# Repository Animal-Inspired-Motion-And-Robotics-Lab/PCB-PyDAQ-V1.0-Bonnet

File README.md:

# Raspberry Pi Data Conversion Board (ADC, DAC, PWM)

<br/>
<br/>

## Description

This board turns your Raspberry Pi into a prototyping powerhouse!  Now your Raspberry Pi can both read and generate analog voltages, in addition to driving PWM waveforms all using existing Python libraries! This repository includes all design files needed to immediately order and assemble the board or make further modifications!

## Features

- 26 Pin IDC Connector for easy prototyping
- 2x STEMMA QT compatible connectors (I2C, +3.3V and GND)
- 4x 12 bit ADC, DAC and PWM channels
- Easy access to SPI, I2C, UART and GPIO
- 2x general purpose PWM controlled LEDs 

## Pinout

### JP1 Connector Pinout <br/> <br/>

<br/> <br/>

| Pin | Signal
| --- | --- |
|1	|GND|
|2	|RXD 
|3	|+3.3V 
|4	|TXD | 
|5	|PWM0
|6	|PWM1
|7	|PWM2
|8	|PWM3
|9	|DAC0
|10	|DAC1
|11	|DAC2
|12	|DAC3
|13	|GPIO17
|14	|GPIO18
|15	|GND
|16	|GPIO22
|17	|SDA
|18	|SCL
|19	|+3.3V
|20	|ADC2
|21	|ADC3
|22	|ADC4
|23	|SPI_MOSI
|24	|ADC5
|25	|SPI_SCLK
|26	|SPI_MISO

## Python Drivers <br/> <br/>

The Proto-Pi board uses Python based drivers to control the ADC, DAC and PWM integrated circuits.  Make sure to install the Adafruit CircuitPython, and required dependencies [(instructions)](https://learn.adafruit.com/circuitpython-on-raspberrypi-linux/installing-circuitpython-on-raspberry-pi) before installing the following drivers: 

- [MCP4728](https://github.com/adafruit/Adafruit_CircuitPython_MCP4728) (12-bit, Quad DAC)
- [MCP3008](https://pypi.org/project/adafruit-circuitpython-mcp3xxx/ )  (10-bit, 8-Channel ADC )
- [PCA9685](https://github.com/adafruit/Adafruit_CircuitPython_PCA9685) (12-bit, 16-Channel PWM)

## Datasheets!

- [MCP4728](http://ww1.microchip.com/downloads/en/devicedoc/22187e.pdf) (12-bit, Quad DAC)
- [MCP3008](https://ww1.microchip.com/downloads/en/DeviceDoc/21295d.pdf)  (10-bit, 8-Channel ADC )
- [PCA9685](https://www.nxp.com/docs/en/data-sheet/PCA9685.pdf) (12-bit, 16-Channel PWM)

## License

The original board shape and connector pinout was based on the amazing [Adafruit Prototype Bonnet](https://www.adafruit.com/product/3203). Thanks Adafruit!

This work is licensed under the Creative Commons Attribution-ShareAlike 4.0 International License. To view a copy of this license, visit http://creativecommons.org/licenses/by-sa/4.0/ or send a letter to Creative Commons, PO Box 1866, Mountain View, CA 94042, USA.

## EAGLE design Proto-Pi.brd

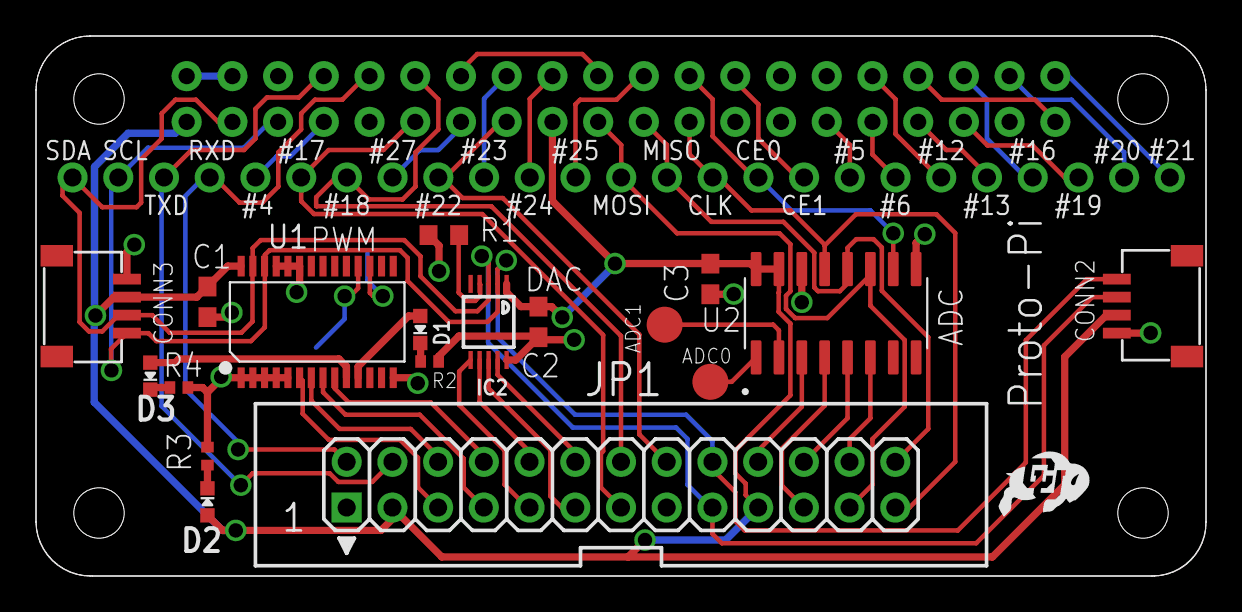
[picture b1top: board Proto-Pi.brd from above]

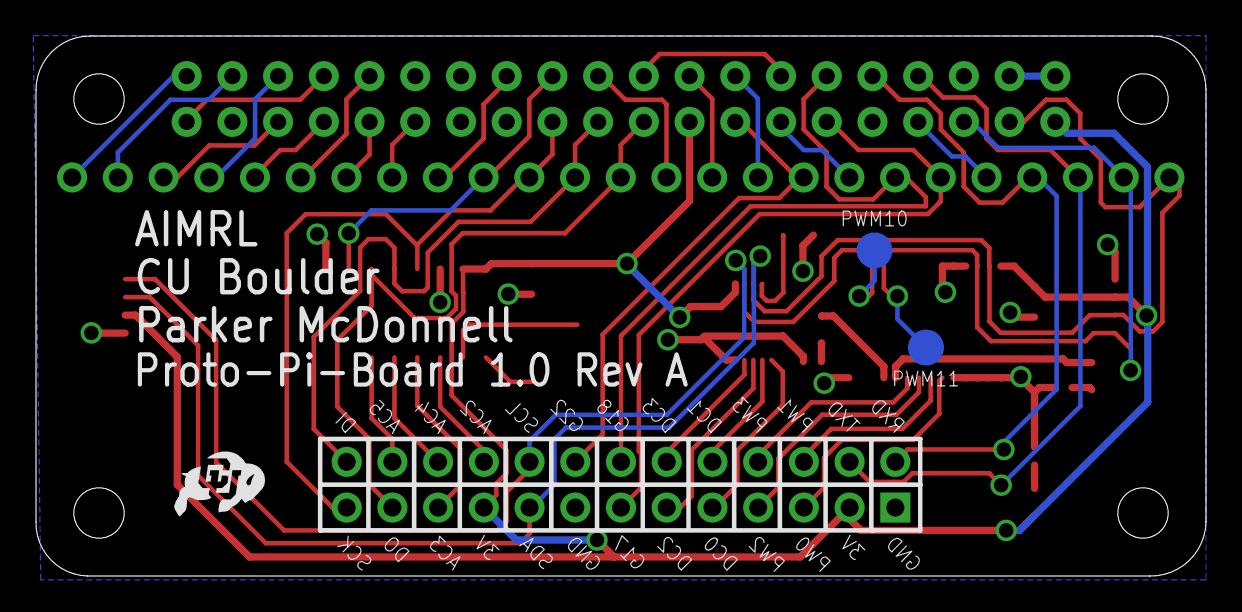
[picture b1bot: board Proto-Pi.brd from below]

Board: 2 copper layers, 65.0 x 30.0 mm, 24 parts (3 on the bottom side), 50 nets.

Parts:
ADC0, ADC1: TPTP20R; TP20R
C1, C2, C3: .1uF; C0603
CONN1: CON-HEADER-1X25; 1X25_ROUND_70MIL
CONN2, CONN3: CON-STEMMA_I2C_QT; JST_SH4
D1, D2, D3: CHIPLED_0603_NOOUTLINE
IC2: DAC-MCP4728; MSOP10
JP1: RASBERRYPI_IDC
P1, P2: ART-CU-LOGO; CU_LOGO
PWM10, PWM11: TPTP20R; TP20R
R1: 10K; R0603
R2, R3, R4: R0402
RPI1: BRD-RASPBERRYPI_BPLUS_BONNETNODIM; PI_BONNET_NODIM
U1: IC-PCA9685PW; TSSOP28-0.65-9.7X4.4MM
U2: ADC-MCP3008; SOIC127P600X175-16N

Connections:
+3.3V: C1.1, C2.1, C3.1, CONN2.2, CONN3.2, D2.A, IC2.1, JP1.3, JP1.19, RPI1.1, RPI1.17, U1.28, U2.15, U2.16
+5.0V: RPI1.2, RPI1.4
ADC0: ADC0.TP, U2.1
ADC1: ADC1.TP, U2.2
ADC2: JP1.20, U2.3
ADC3: JP1.21, U2.4
ADC4: JP1.22, U2.5
ADC5: JP1.24, U2.6
DAC0: IC2.6, JP1.9
DAC1: IC2.7, JP1.10
DAC2: IC2.8, JP1.11
DAC3: IC2.9, JP1.12
GND: C1.2, C2.2, C3.2, CONN2.1, CONN3.1, IC2.10, JP1.1, JP1.15, R1.1, R2.1, R3.2, R4.2, RPI1.6, RPI1.9, RPI1.14, RPI1.20, RPI1.25, RPI1.30, RPI1.34, RPI1.39, U1.1, U1.2, U1.3, U1.4, U1.5, U1.14, U1.23, U1.24, U1.25, U2.9, U2.14
GPIO4: CONN1.5, RPI1.7
GPIO5: CONN1.18, RPI1.29
GPIO6: CONN1.19, RPI1.31
GPIO12: CONN1.20, RPI1.32
GPIO13: CONN1.21, RPI1.33
GPIO16: CONN1.22, RPI1.36
GPIO17: CONN1.6, JP1.13, RPI1.11
GPIO18: CONN1.7, JP1.14, RPI1.12
GPIO19: CONN1.23, RPI1.35
GPIO20: CONN1.24, RPI1.38
GPIO21: CONN1.25, RPI1.40
GPIO22: CONN1.9, JP1.16, RPI1.15
GPIO23: CONN1.10, RPI1.16
GPIO24: CONN1.11, RPI1.18
GPIO25: CONN1.12, RPI1.22
GPIO27: CONN1.8, RPI1.13
LDAC: IC2.4, R1.2
unnamed: D1.C, R2.2
unnamed: D2.C, R3.1
unnamed: D3.C, R4.1
PWM0: JP1.5, U1.6
PWM1: JP1.6, U1.7
PWM2: JP1.7, U1.8
PWM3: JP1.8, U1.9
PWM4: D3.A, U1.10
PWM5: D1.A, U1.11
PWM10: PWM10.TP, U1.17
PWM11: PWM11.TP, U1.18
RXD: CONN1.4, JP1.2, RPI1.10
SCL: CONN1.2, CONN2.4, CONN3.4, IC2.2, JP1.18, RPI1.5, U1.26
SDA: CONN1.1, CONN2.3, CONN3.3, IC2.3, JP1.17, RPI1.3, U1.27
SPI_CE0: CONN1.16, RPI1.24, U2.10
SPI_CE1: CONN1.17, RPI1.26
SPI_MISO: CONN1.14, JP1.26, RPI1.21, U2.12
SPI_MOSI: CONN1.13, JP1.23, RPI1.19, U2.11
SPI_SCLK: CONN1.15, JP1.25, RPI1.23, U2.13
TXD: CONN1.3, JP1.4, RPI1.8

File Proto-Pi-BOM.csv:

Line Item,Reference Designator,Package,Value,Part Number,Mouser PN
1,JP1,RASBERRYPI_IDC,,,
2,"D1, D2, D3",CHIPLED_0603_NOOUTLINE,,,
3,"R2, R3, R4",R0402,,,
4,"C1, C2, C3",C0603,.1uF,,
5,R1,R0603,10K,,
6,U2,,ADC-MCP3008,,
9,CONN1,,CON-HEADER-1X25,,
10,"CONN2, CONN3",JST_SH4,CON-STEMMA_I2C_QT,,
11,IC2,MSOP10,DAC-MCP4728,MCP4728A1T-E,579-MCP4728A1T-E
12,U1,TSSOP28,IC-PCA9685PW,"PCA9685PW,118",771-PCA9685PW

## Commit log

2021-12-27 Big Commit!
    Updated the readme, added design files, photos and 3D CAD
2021-12-28 Updated the design, created new photos and CAD
2022-01-21 Created soldermask top stencil and PDFs for layout and schematic
2022-03-13 added BOM, pinout and datasheets
2022-03-16 Major Update
    Added picture of JP1 connector, and added pinout to readme.
2022-04-03 Created Altium library
2022-04-03 Updated BOM and readme
2022-04-04 Added CAM outputs
2022-04-04 added stuff
2022-04-09 Update README.md
    Added links to documentation and drivers for the ADC, DAC and PWM ICs.
2022-04-14 created drill files
2022-04-22 Added datasheets w/links
2022-04-22 Created Proto-Pi.py file
    Initial Proto-Pi python library. Will break this up into a library that can be imported and used easily.
2023-02-22 Wrote basic code for talking to FDC2214, HV56020 and driving the DACs
2023-09-07 Adjusted folder paths and added MCP3008 datasheet and orderable fabrication files all zipped up.
2023-09-07 Update README.md
    updated readme
2023-09-07 Updated readme with credit to Adafruit for original PCB outline
